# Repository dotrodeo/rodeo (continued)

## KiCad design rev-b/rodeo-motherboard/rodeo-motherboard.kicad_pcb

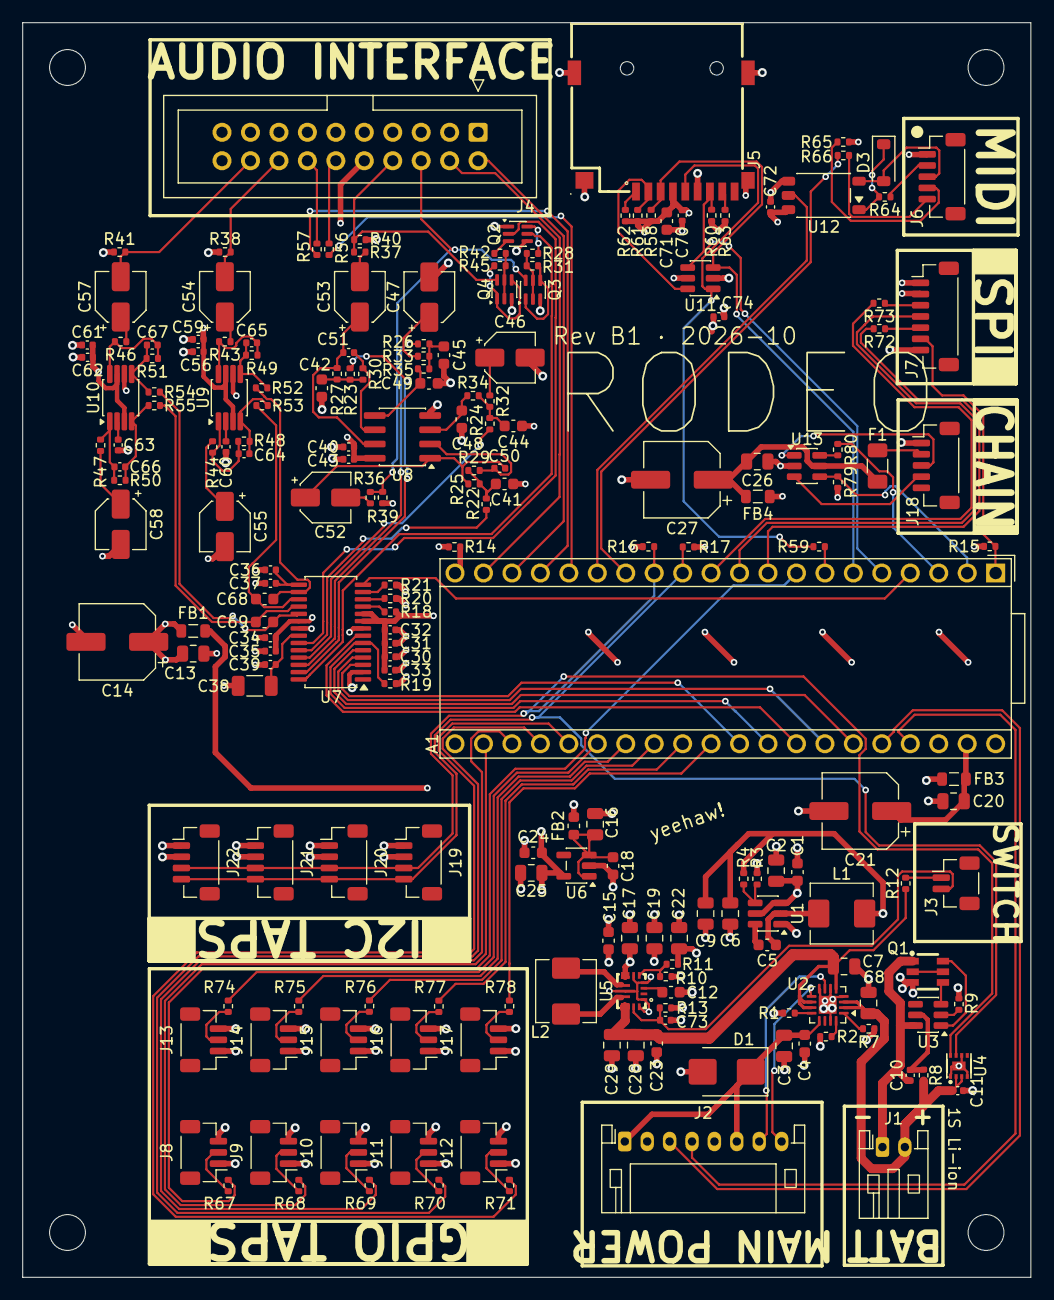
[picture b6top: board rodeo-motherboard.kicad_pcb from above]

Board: 4 copper layers, 90.0 x 112.0 mm, 205 parts (0 on the bottom side), 147 nets.

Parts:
A1: Electrosmith_Daisy_Seed_Rev4; Electrosmith_Daisy_Seed
C1, C5: 0.1u; C_0603_1608Metric
C2, C3, C13, C16, C20, C25, C26, C28, C29: 10u; C_0805_2012Metric
C4, C18, C24: 1u; C_0603_1608Metric
C6, C9, C17, C19, C22: 22u; C_0805_2012Metric
C7, C8: 4.7u; C_0805_2012Metric
C10, C30, C32, C34, C37, C39, C43, C59, C60, C62, C63, C70, C72, C74: 0.1u; C_0402_1005Metric
C11, C31, C33, C35, C36, C40, C56, C61: 1u; C_0402_1005Metric
C12: 100n; C_0603_1608Metric
C14, C21, C27: 100u; CP_Elec_6.3x5.4
C15, C23, C71: 10u; C_0603_1608Metric
C38: 47u; C_1206_3216Metric
C41, C42: 2.2n; C_0603_1608Metric
C44, C45: 6.8n; C_0603_1608Metric
C46, C47, C52, C53: 22u; CP_Elec_4x5.4
C48, C49: 1.5n; C_0603_1608Metric
C50, C51: 470p; C_0402_1005Metric
C54, C55, C57, C58: 10u; CP_Elec_4x5.4
C64, C65, C66, C67: 150p; C_0402_1005Metric
C68, C69: 2.7n; C_0603_1608Metric
C73: 10n; C_0402_1005Metric
D1: SMBJ5.0A; D_SMB
D3: 1N4148W; D_SOD-123
F1: nSMD075; Fuse_1206_3216Metric
FB1, FB3, FB4: BLM21PG221SN1D; L_0805_2012Metric
FB2: BLM18KG601SN1D; L_0603_1608Metric
H1, H2, H3, H4: MountingHole; MountingHole_3.2mm_M3
J1: Conn_01x02; JST_PH_S2B-PH-K_1x02_P2.00mm_Horizontal
J2: Conn_01x08; JST_PH_S8B-PH-K_1x08_P2.00mm_Horizontal
J3: Conn_01x02; JST_SH_BM02B-SRSS-TB_1x02-1MP_P1.00mm_Vertical
J4: Conn_02x10_Odd_Even; IDC-Header_2x10_P2.54mm_Vertical
J5: TF PUSH; TF-SMD_TF-PUSH
J6, J18: Conn_01x05; JST_SH_BM05B-SRSS-TB_1x05-1MP_P1.00mm_Vertical
J7: Conn_01x07; JST_SH_BM07B-SRSS-TB_1x07-1MP_P1.00mm_Vertical
J8, J9, J10, J11, J12, J13, J14, J15, J16, J17: Conn_01x03; JST_SH_BM03B-SRSS-TB_1x03-1MP_P1.00mm_Vertical
J19, J20, J21, J22: Conn_01x04; JST_SH_BM04B-SRSS-TB_1x04-1MP_P1.00mm_Vertical
L1: 2.2uH; L_Sunlord_MWSA0518S
L2: 1.5uH; L_Sunlord_MWSA0518S
Q1: FS8205A; SOT-23-6_L2.9-W1.6-P0.95-LS2.8-BR
Q2: BSS84DW; SOT-363_SC-70-6
Q3, Q4: 2N7002DW; SOT-363_SC-70-6
R1: 1.18K; R_0402_1005Metric
R2: 1.13K; R_0402_1005Metric
R3, R7, R12, R15, R18, R20, R21, R28, R42, R79: 10K; R_0402_1005Metric
R4: 33K2; R_0402_1005Metric
R8, R56, R57, R65, R66: 100R; R_0402_1005Metric
R9, R67, R68, R69, R70, R71, R74, R75, R76, R77, R78: 1K; R_0402_1005Metric
R10: 19K1; R_0402_1005Metric
R11: 100K; R_0402_1005Metric
R13, R31, R38, R41, R45: 1M; R_0402_1005Metric
R14: 0R; R_0402_1005Metric
R16, R17: 2K2; R_0402_1005Metric
R19, R39, R40, R58, R60, R61, R62, R63: 47K; R_0402_1005Metric
R22, R23: 4K42; R_0402_1005Metric
R24, R26: 1K33; R_0402_1005Metric
R25, R27: 4K99; R_0402_1005Metric
R29, R30: 2K32; R_0402_1005Metric
R32, R33: 1K5; R_0402_1005Metric
R34, R35: 715R; R_0402_1005Metric
R36, R37: 560R; R_0402_1005Metric
R43, R44, R46, R47: 7K5; R_0402_1005Metric
R48, R49, R50, R51: 10K5; R_0402_1005Metric
R52, R53, R54, R55: 91R; R_0402_1005Metric
R59: 22R; R_0402_1005Metric
R64: 220R; R_0402_1005Metric
R72, R73, R80: 33R; R_0402_1005Metric
U1: TPS563208; TSOT-23-6
U2: BQ24073RGT; VQFN-16-1EP_3x3mm_P0.5mm_EP1.6x1.6mm
U3: DW01A; SOT-23-6
U4: MAX17048G+T10; TDFN-8_L2.0-W2.0-P0.50-BL-EP1.2
U5: TPS63070RNMR; VQFN-15_L3.0-W2.5-P0.50-BL
U6: TPS7A2033PDBVR; SOT-23-5
U7: CS4272; TSSOP-28_4.4x9.7mm_P0.65mm
U8: OPA2376xxD; SOIC-8_3.9x4.9mm_P1.27mm
U9, U10: THS4521IDGK; VSSOP-8_3x3mm_P0.65mm
U11: SRV05-4; SOT-23-6
U12: TLP2361; SO-5-6_4.55x3.7mm_P1.27mm
U13: USBLC6-2SC6; SOT-23-6

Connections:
+3V3_A: C24.2, C25.2, J7.7, J8.3, J9.3, J10.3, J11.3, J12.3, J13.3, J14.3, J15.3, J16.3, J17.3, U6.5 (OUT)
+3V3_D: C6.2, C9.2, C30.2, C31.2, C32.2, C33.2, C70.1, C71.1, C72.2, C74.1, FB4.1, J5.4 (VDD), J7.1, J19.2, J20.2, J21.2, J22.2, L1.2, R4.2, R15.2, R16.1, R17.1, R18.2, R58.1, R60.1, R61.1, R62.1, R63.1, R65.2, R79.2, U7.9 (VD), U7.10 (VL), U11.5 (VP), U12.6 (VDD)
+3V3_SAT: C26.2, C27.1, F1.2, FB4.2, U13.5 (VBUS)
+5V_A: C13.2, C14.1, C34.2, C35.2, C40.2, C43.1, C56.2, C59.1, C61.2, C62.1, FB1.2, J4.10, Q2.1 (S), Q2.4 (S), U7.20 (VA), U8.8 (V+), U9.3 (V_{S+}), U9.7 (~PD), U10.3 (V_{S+}), U10.7 (~PD)
+5V_SYS: C1.1, C2.1, C15.1, C17.1, C19.1, C22.1, FB1.1, FB2.1, FB3.1, R11.2, U1.3 (VIN), U1.5 (EN), U5.7 (Vout)
AUDIO_IN_1: A1.16 (AUDIO_IN_1), R56.1
AUDIO_IN_2: A1.17 (AUDIO_IN_2), R57.1
AUDIO_OUT_1: A1.18 (AUDIO_OUT_1), J4.2
AUDIO_OUT_2: A1.19 (AUDIO_OUT_2), J4.4
BATT_N: C10.1, J1.1, Q1.1 (S1), U3.6 (GND)
BATT_P: C8.1, C11.1, J1.2, R8.1, U2.2 (BAT), U2.3 (BAT), U4.2 (CELL), U4.3 (VDD)
BATT_VCC: C7.1, C23.1, C28.1, C29.1, R12.1, U2.5 (EN2), U2.10 (OUT), U2.11 (OUT), U5.12 (Vin)
CLK: J5.5 (CLK), R59.1, U11.1 (IO1)
CODEC2_AINA_N: C68.2, R52.1, U7.16 (AINA-)
CODEC2_AINA_P: C68.1, R53.1, U7.17 (AINA+)
CODEC2_AINB_N: C69.2, R54.1, U7.19 (AINB-)
CODEC2_AINB_P: C69.1, R55.1, U7.18 (AINB+)
CODEC2_AOUTA_N: R22.1, U7.24 (AOUTA-)
CODEC2_AOUTA_P: R24.1, U7.25 (AOUTA+)
CODEC2_AOUTB_N: R23.1, U7.27 (AOUTB-)
CODEC2_AOUTB_P: R26.1, U7.26 (AOUTB+)
CODEC2_IN_A: C54.2, J4.16, R38.2
CODEC2_IN_B: C57.2, J4.18, R41.2
CODEC2_LRCK: A1.34 (SAI2_FS), U7.4 (LRCK)
CODEC2_MCLK: A1.31 (SAI2_MCLK), U7.3 (MCLK)
CODEC2_MUTE_A: Q2.2 (G), U7.23 (~AMUTEC)
CODEC2_MUTE_B: Q2.5 (G), U7.28 (~BMUTEC)
CODEC2_OUT_A: J4.6, Q3.6 (D), R36.1, R39.1
CODEC2_OUT_B: J4.8, Q4.6 (D), R37.1, R40.1
CODEC2_RST: A1.4 (SD_DATA_1), U7.14 (~RST)
CODEC2_SCLK: A1.35 (SAI2_SCK), U7.5 (SCLK)
CODEC2_SDIN: A1.33 (SAI2_SD_A), U7.7 (SDIN)
CODEC2_SDOUT: A1.32 (SAI2_SD_B), R19.2, U7.6 (SDOUT(M/~S))
CODEC2_VCOM: C36.2, C37.2, U7.15 (VCOM)
CV_DAC1: A1.30 (DAC_OUT1), R78.2
CV_DAC2: A1.29 (DAC_OUT2), R77.2
DAISY_SCL: A1.12 (I2C1_SCL), J19.4, J20.4, J21.4, J22.4, R17.2, U4.7 (SCL)
DAISY_SDA: A1.13 (I2C1_SDA), J19.3, J20.3, J21.3, J22.3, R16.2, U4.8 (SDA)
DAT3: J5.2 (CD/DAT3), R61.2, U11.6 (IO4)
DIG_1: A1.8 (SPI1_CS), R67.2
DIG_2: A1.22 (ADC_0), R68.2
DIG_3: A1.23 (ADC_1), R69.2
DIG_4: A1.24 (ADC_2), R70.2
DIG_5: A1.25 (ADC_3), R71.2
DIG_6: A1.26 (ADC_4), R74.2
DIG_7: A1.27 (ADC_5), R75.2
DIG_8: A1.28 (ADC_6), R76.2
GND: A1.40 (DGND), C1.2, C2.2, C3.2, C4.2, C6.1, C7.2, C8.2, C9.1, C11.2, C12.2, C13.1, C14.2, C15.2, C16.1, C17.2, C18.1, C19.2, C20.1, C21.2, C22.2, C23.2, C24.1, C25.1, C26.1, C27.2, C28.2, C29.2, C30.1, C31.1, C32.1, C33.1, C34.1, C35.1, C36.1, C37.1, C38.2, C39.1, C40.1, C41.2, C42.2, C43.2, C44.1, C45.1, C46.2, C47.2, C48.2, C49.2, C55.2, C56.1, C58.2, C59.2, C60.2, C61.1, C62.2, C63.2, C70.2, C71.2, C72.1, C73.1, C74.2, D1.2 (A), J2.2, J2.5, J4.1, J4.3, J4.5, J4.7, J4.9, J4.11, J4.13, J4.15, J4.17, J4.19, J5.6 (VSS), J5.10, J5.11, J5.12, J5.13, J6.1, J7.2, J8.1, J9.1, J10.1, J11.1, J12.1, J13.1, J14.1, J15.1, J16.1, J17.1, J18.1, J19.1, J20.1, J21.1, J22.1, Q1.3 (S2), Q3.3 (D), Q4.3 (D), R1.1, R2.1, R3.1, R7.2, R9.2, R10.1, R13.2, R14.1, R19.1, R20.2, R21.2, R38.1, R39.2, R40.2, R41.1, U1.1 (GND), U2.4 (~CE), U2.6 (EN1), U2.8 (VSS), U2.15 (TD), U2.17 (VSS), U4.1 (CTG), U4.4 (GND), U4.6 (QSTRT), U4.9 (EP), U5.1 (PS/SYNC), U5.4 (GND), U5.6 (FB2), U5.10 (PGND), U5.15 (Vsel), U6.2 (GND), U7.2 (XTI), U7.8 (DGND), U7.21 (AGND), U8.4 (V-), U9.6 (V_{S-}), U10.6 (V_{S-}), U11.2 (VN), U12.4 (GND), U13.2 (GND)
GNDA: A1.20 (AGND), R14.2
JACK_IN_1: J4.12, R56.2
JACK_IN_2: J4.14, R57.2
MIDI_IN_R: J6.2, R64.1
MIDI_IN_T: D3.2 (A), J6.3, U12.3 (K)
MIDI_OUT_R: J6.4, R65.1
MIDI_OUT_T: J6.5, R66.1
MIDI_RX: A1.15 (USART1_RX), U12.5 (VO)
MIDI_TX: A1.14 (USART1_TX), R66.2
unnamed: C41.1, R22.2, R25.1, R29.1
unnamed: C42.1, R23.2, R27.1, R30.1
unnamed: C44.2, R24.2, R32.2, R34.2
unnamed: C45.2, R26.2, R33.2, R35.2
unnamed: C46.1, R32.1
unnamed: C47.1, R33.1
unnamed: C50.1, C52.1, R25.2, U8.1
unnamed: C51.1, C53.1, R27.2, U8.7
unnamed: C52.2, R36.2
unnamed: C53.2, R37.2
unnamed: C54.1, R43.1
unnamed: C55.1, R44.1
unnamed: C57.1, R46.1
unnamed: C58.1, R47.1
unnamed: C64.2, R48.2, R53.2, U9.4
unnamed: C65.1, R49.2, R52.2, U9.5
unnamed: C66.2, R50.2, R55.2, U10.4
unnamed: C67.1, R51.2, R54.2, U10.5
unnamed: D3.1 (K), R64.2, U12.1 (A)
unnamed: J3.1, R12.2
unnamed: C73.2, J3.2, R13.1, U5.14 (EN)
unnamed: J5.8 (DAT1), R63.2
unnamed: J5.1 (DAT2), R62.2
unnamed: J7.3, R73.1
unnamed: J7.5, R72.1
unnamed: J8.2, R67.1
unnamed: J9.2, R68.1
unnamed: J10.2, R69.1
unnamed: J11.2, R70.1
unnamed: J12.2, R71.1
unnamed: J13.2, R74.1
unnamed: J14.2, R75.1
unnamed: J15.2, R76.1
unnamed: J16.2, R77.1
unnamed: J17.2, R78.1
unnamed: F1.1, J18.2
unnamed: J18.3, U13.1 (I/O1)
unnamed: J18.4, U13.3 (I/O2)
unnamed: Q1.2 (D1/D2), Q1.5 (D1/D2)
unnamed: Q1.6 (G1), U3.1 (OD)
unnamed: Q1.4 (G2), U3.3 (OC)
unnamed: Q2.6 (D), R28.2
unnamed: Q2.3 (D), R42.2
unnamed: Q3.2 (G), Q3.5 (G), R28.1, R31.1
unnamed: Q3.1 (S), Q3.4 (S), R31.2
unnamed: Q4.2 (G), Q4.5 (G), R42.1, R45.1
unnamed: Q4.1 (S), Q4.4 (S), R45.2
unnamed: R80.1, U13.6 (I/O1)
unnamed: C5.2, L1.1, U1.2 (SW)
unnamed: C5.1, U1.6 (VBST)
unnamed: R3.2, R4.1, U1.4 (VFB)
unnamed: R1.2, U2.12 (ILIM)
unnamed: R2.2, U2.16 (ISET)
unnamed: R7.1, U2.1 (TS)
unnamed: R9.1, U3.2 (CS)
unnamed: C10.2, R8.2, U3.5 (VCC)
unnamed: R10.2, R11.1, U5.5 (FB)
unnamed: L2.1, U5.11 (L1)
unnamed: L2.2, U5.9 (L2)
unnamed: C12.1, U5.3 (Vaux)
unnamed: C16.2, C18.2, FB2.2, U6.1 (IN), U6.3 (EN)
unnamed: R21.1, U7.13 (AD0/~CS(I2S/~LJ))
unnamed: C38.1, C39.2, U7.22 (FILT+)
unnamed: R18.1, U7.11 (SCL/CCLK(M0))
unnamed: R20.1, U7.12 (SDA/CDIN(M1))
unnamed: C48.1, R34.1, U8.3 (+)
unnamed: C50.2, R29.2, U8.2 (-)
unnamed: C49.1, R35.1, U8.5 (+)
unnamed: C51.2, R30.2, U8.6 (-)
unnamed: C65.2, R43.2, R49.1, U9.8 (+)
unnamed: C64.1, R44.2, R48.1, U9.1 (-)
unnamed: C60.1, U9.2 (V_{OCM})
unnamed: C67.2, R46.2, R51.1, U10.8 (+)
unnamed: C66.1, R47.2, R50.1, U10.1 (-)
unnamed: C63.1, U10.2 (V_{OCM})
SAT_RX: A1.2 (SD_DATA_3), R79.1, U13.4 (I/O2)
SAT_TX: A1.3 (SD_DATA_2), R80.2
SD_CLK: A1.7 (SD_CLK), R59.2
SD_CMD: A1.6 (SD_CMD), J5.3 (CMD), R58.2, U11.3 (IO2)
SD_D_0: A1.5 (SD_DATA_0), J5.7 (DAT0), R60.2, U11.4 (IO3)
SEED_VIN: A1.39 (VIN), C20.2, C21.1, FB3.2
SPI_EXT_CS: A1.1 (USB_ID), J7.6, R15.1
SPI_MISO: A1.10 (SPI1_POCI), J7.4
SPI_MOSI: A1.11 (SPI1_PICO), R73.2
SPI_SCK: A1.9 (SPI1_SCK), R72.2
USB_OTG_HS_N: A1.36 (USB_D_-), J2.3
USB_OTG_HS_P: A1.37 (USB_D_+), J2.4
VIN: C3.1, C4.1, D1.1 (K), J2.1, J2.6, U2.13 (IN)
~CHG: J2.8, U2.9 (~CHG)
~PGOOD: J2.7, U2.7 (~PGOOD)

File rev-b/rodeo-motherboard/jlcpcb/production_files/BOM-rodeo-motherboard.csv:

Comment,Designator,Footprint,LCSC,Quantity
0.1u,"C1,C5",C_0603_1608Metric,C14663,2
10u,"C2,C3,C13,C16,C20,C25,C26,C28,C29",C_0805_2012Metric,C15850,9
1u,"C4,C18,C24",C_0603_1608Metric,C15849,3
22u,"C6,C9,C17,C19,C22",C_0805_2012Metric,C45783,5
4.7u,"C7,C8",C_0805_2012Metric,C1779,2
0.1u,"C10,C30,C32,C34,C37,C39,C43,C59,C60,C62,C63,C70,C72,C74",C_0402_1005Metric,C1525,14
1u,"C11,C31,C33,C35,C36,C40,C56,C61",C_0402_1005Metric,C52923,8
100n,C12,C_0603_1608Metric,C14663,1
100u,"C14,C21,C27",CP_Elec_6.3x5.4,C2887276,3
10u,"C15,C23,C71",C_0603_1608Metric,C96446,3
47u,C38,C_1206_3216Metric,C96123,1
2.2n,"C41,C42",C_0603_1608Metric,C296055,2
6.8n,"C44,C45",C_0603_1608Metric,C513559,2
22u,"C46,C47,C52,C53",CP_Elec_4x5.4,C72502,4
1.5n,"C48,C49",C_0603_1608Metric,C107039,2
470p,"C50,C51",C_0402_1005Metric,C106259,2
10u,"C54,C55,C57,C58",CP_Elec_4x5.4,C72484,4
150p,"C64,C65,C66,C67",C_0402_1005Metric,C541469,4
2.7n,"C68,C69",C_0603_1608Metric,C388043,2
10n,C73,C_0402_1005Metric,C15195,1
SMBJ5.0A,D1,D_SMB,C113974,1
1N4148W,D3,D_SOD-123,C81598,1
nSMD075,F1,Fuse_1206_3216Metric,C70078,1
BLM21PG221SN1D,"FB1,FB3,FB4",L_0805_2012Metric,C85840,3
BLM18KG601SN1D,FB2,L_0603_1608Metric,C85833,1
Conn_01x02,J1,JST_PH_S2B-PH-K_1x02_P2.00mm_Horizontal,C173752,1
Conn_01x08,J2,JST_PH_S8B-PH-K_1x08_P2.00mm_Horizontal,C157915,1
Conn_01x02,J3,JST_SH_BM02B-SRSS-TB_1x02-1MP_P1.00mm_Vertical,C160388,1
Conn_02x10_Odd_Even,J4,IDC-Header_2x10_P2.54mm_Vertical,C2977593,1
TF PUSH,J5,TF-SMD_TF-PUSH,C393941,1
Conn_01x05,"J6,J18",JST_SH_BM05B-SRSS-TB_1x05-1MP_P1.00mm_Vertical,C160391,2
Conn_01x07,J7,JST_SH_BM07B-SRSS-TB_1x07-1MP_P1.00mm_Vertical,C160393,1
Conn_01x03,"J8,J9,J10,J11,J12,J13,J14,J15,J16,J17",JST_SH_BM03B-SRSS-TB_1x03-1MP_P1.00mm_Vertical,C160389,10
Conn_01x04,"J19,J20,J21,J22",JST_SH_BM04B-SRSS-TB_1x04-1MP_P1.00mm_Vertical,C160390,4
2.2uH,L1,L_Sunlord_MWSA0518S,C408345,1
1.5uH,L2,L_Sunlord_MWSA0518S,C408344,1
FS8205A,Q1,SOT-23-6_L2.9-W1.6-P0.95-LS2.8-BR,C2830320,1
BSS84DW,Q2,SOT-363_SC-70-6,C161617,1
2N7002DW,"Q3,Q4",SOT-363_SC-70-6,C83571,2
1.18K,R1,R_0402_1005Metric,C270651,1
1.13K,R2,R_0402_1005Metric,C67014,1
10K,"R3,R7,R12,R15,R18,R20,R21,R28,R42,R79",R_0402_1005Metric,C25744,10
33K2,R4,R_0402_1005Metric,C122548,1
100R,"R8,R56,R57,R65,R66",R_0402_1005Metric,C25076,5
1K,"R9,R67,R68,R69,R70,R71,R74,R75,R76,R77,R78",R_0402_1005Metric,C11702,11
19K1,R10,R_0402_1005Metric,C52036,1
100K,R11,R_0402_1005Metric,C25741,1
1M,"R13,R31,R38,R41,R45",R_0402_1005Metric,C26083,5
0R,R14,R_0402_1005Metric,C17168,1
2K2,"R16,R17",R_0402_1005Metric,C25879,2
47K,"R19,R39,R40,R58,R60,R61,R62,R63",R_0402_1005Metric,C25792,8
4K42,"R22,R23",R_0402_1005Metric,C52269,2
1K33,"R24,R26",R_0402_1005Metric,C423242,2
4K99,"R25,R27",R_0402_1005Metric,C25903,2
2K32,"R29,R30",R_0402_1005Metric,C82297,2
1K5,"R32,R33",R_0402_1005Metric,C25867,2
715R,"R34,R35",R_0402_1005Metric,C113474,2
560R,"R36,R37",R_0402_1005Metric,C25126,2
7K5,"R43,R44,R46,R47",R_0402_1005Metric,C25918,4
10K5,"R48,R49,R50,R51",R_0402_1005Metric,C25850,4
91R,"R52,R53,R54,R55",R_0402_1005Metric,C270574,4
22R,R59,R_0402_1005Metric,C25092,1
220R,R64,R_0402_1005Metric,C25091,1
33R,"R72,R73,R80",R_0402_1005Metric,C25105,3
TPS563208,U1,TSOT-23-6,C468250,1
BQ24073RGT,U2,VQFN-16-1EP_3x3mm_P0.5mm_EP1.6x1.6mm,C15220,1
DW01A,U3,SOT-23-6,C351410,1
MAX17048G+T10,U4,TDFN-8_L2.0-W2.0-P0.50-BL-EP1.2,C2682616,1
TPS63070RNMR,U5,VQFN-15_L3.0-W2.5-P0.50-BL,C109322,1
TPS7A2033PDBVR,U6,SOT-23-5,C2862740,1
CS4272,U7,TSSOP-28_4.4x9.7mm_P0.65mm,C2151111,1
OPA2376xxD,U8,SOIC-8_3.9x4.9mm_P1.27mm,C46316,1
THS4521IDGK,"U9,U10",VSSOP-8_3x3mm_P0.65mm,C170157,2
SRV05-4,U11,SOT-23-6,C13612,1
TLP2361,U12,SO-5-6_4.55x3.7mm_P1.27mm,C107626,1
USBLC6-2SC6,U13,SOT-23-6,C7519,1

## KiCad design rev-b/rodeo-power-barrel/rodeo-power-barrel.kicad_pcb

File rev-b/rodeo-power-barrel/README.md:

# Rodeo power board: USB-C + barrel jack

Everything the [USB-C board](../rodeo-power-usbc/README.md) does, plus a barrel
jack for a 9–12 V adapter and a separate 5 V output for LED strips. When the
adapter is plugged in it powers the motherboard; USB stays connected for data
and takes over if the adapter is removed. The contract it meets is in
[`rev-b.md`, "Power"](../rodeo-motherboard/docs/rev-b.md#power).

Designed 2026-10-12. Mounting as the USB-C board: jacks and LEDs on the I/O edge, the board on
the [rear rail](../mounting/README.md) on M3 × 8 mm standoffs.

```
Barrel 7–20 V ─ Q1 reverse-polarity P-FET ─ VBARREL ─┬─ U3 TPS54308 ─ +5V_BRL ─┐
               (TVS D5, bulk C2)                    │                        ├─ U4 TPS2121 ─ VIN ─ J2 (motherboard)
USB-C VBUS ─────────────────────────────────────────┼────────────────────────┘   barrel first
                                                    └─ U2 TPS54302 ─ +5V_AUX ─ F1 3 A PTC ─ J4 (LED strips)
```

## Adapter

5.5 × 2.1 mm plug, **centre positive**, 7–20 V (9 V or 12 V adapters). Full load
is the motherboard (≤1.5 A at 5 V) plus the aux output (≤3 A at 5 V), about
25 W in: **12 V ≥ 2.5 A or 9 V ≥ 3 A**. Smaller adapters work if the aux output
is lightly loaded.

## Connections

Reference designators below are the schematic's (drawn 2026-10-13).

**USB-C section:** identical to the USB-C board (J1, R1/R2 5.1 kΩ CC pull-downs,
U1 USBLC6 flow-through on D+/D−, D3 SMF5.0A and C1 4.7 µF on `VBUS`), except that
`VBUS` goes to the mux (U4 IN2) instead of straight to J2.

**J3, barrel jack: CUI PJ-102AH (C3096093), 5 A, 2.0 mm pin.** Symbol
`Connector:Barrel_Jack_Switch`, footprint
`Connector_BarrelJack:BarrelJack_CUI_PJ-102AH_Horizontal`.

| J3 pin | Net |
|---|---|
| 1 (centre pin) | `BARREL_IN` |
| 2 (sleeve) | `GND` |
| 3 (switch) | no connect: it opens when a plug is inserted, so it must not carry GND |

**Reverse-polarity protection and input filtering.** Only Q1's drain is on the
jack side; everything else is on `VBARREL`, after Q1.

| Part | Connection |
|---|---|
| Q1 AO4407A P-FET, 30 V 12 A (C2841482), symbol `rodeo_power:AO4407A`, SOIC-8 | drain (5–8) `BARREL_IN`; source (1–3) `VBARREL`; gate (4) → R5 100 kΩ to `GND` |
| D4 BZT52C12 12 V Zener (C173429), SOD-123 | cathode `VBARREL`, anode Q1 gate: holds V_GS within −12 V |
| D5 SMBJ20A TVS (C364296), SMB | cathode `VBARREL`, anode `GND` (after Q1, so a reversed adapter can't drive it) |
| C2 47 µF 35 V electrolytic (C72522), 6.3 × 5.4 | `VBARREL` (+) to `GND`: bulk, damps the adapter cable |

With the adapter the right way round, Q1's body diode conducts first, then its
gate is pulled 9–12 V below its source and it turns fully on (≈14 mΩ). Reversed,
the body diode blocks and the gate sits at the source, so Q1 stays off. The
Zener must sit between gate and **source**: tied to the drain it would conduct
with a reversed adapter and turn Q1 on.

**U3, motherboard 5 V: TPS54308 (C168839), 3 A, fixed 350 kHz.** Symbol
`Regulator_Switching:TPS54302` (same pinout; Value TPS54308).

| U3 pin | Connection |
|---|---|
| 3 VIN | `VBARREL`, with 2 × 10 µF 50 V 1206 (C513774) + 0.1 µF 50 V 0603 (C14663) to `GND` at the pin |
| 1 GND | `GND` |
| 5 EN | no connect (internal pull-up enables it) |
| 6 BOOT | C4 0.1 µF 50 V (C14663) to SW |
| 2 SW | L2 10 µH (Sunlord MWSA0603S-100MT, C132141) → `+5V_BRL` |
| 4 FB | R9 100 kΩ from `+5V_BRL`, R8 13.3 kΩ to `GND`: 0.596 × (1 + 100/13.3) = 5.08 V |
| output | C15, C16 22 µF 25 V 0805 (C45783) on `+5V_BRL` |

**U2, LED aux 5 V: TPS54302 (C311983), 3 A.** Same circuit and values as U3:
boot C3, L1, FB R6 100 kΩ / R7 13.3 kΩ, output C17, C18 on `+5V_AUX`. The
TPS54302 pulse-skips at light load, which is efficient and doesn't matter for
LEDs; the motherboard supply uses the fixed-frequency TPS54308 instead.

The buck input caps C9–C14 (four 10 µF, two 0.1 µF) are all on `VBARREL`: in
layout, put one 0.1 µF and two 10 µF at each buck's VIN/GND, 0.1 µF closest.

| Part | Connection |
|---|---|
| F1 3 A PTC, 6 A trip, 1812 (TLC-MSMD300, C262035) | `+5V_AUX` → `AUX_OUT` |
| J4 JST VH 2-pin vertical, B2P-VH (C160315), 10 A | pin 1 `AUX_OUT`, pin 2 `GND` |

**U4, source mux: TPS2121 (C485916), barrel first.** Symbol
`rodeo_power:TPS2121RUXR`. Same configuration the motherboard used before the
mux moved here.

| U4 pin | Connection |
|---|---|
| 7 IN1 (priority) | `+5V_BRL`, C5 1 µF (C15849) to `GND` |
| 2 IN2 | `VBUS`, C6 1 µF (C15849) to `GND` |
| 6 PR1 | R11 28 kΩ from `+5V_BRL`, R10 15 kΩ to `GND` |
| 3 CP2 | R13 34 kΩ from `VBUS`, R12 15 kΩ to `GND` |
| 1, 8 OUT | `VIN`, C8 10 µF 25 V 0805 (C15850) to `GND` |
| 10 ILM | R14 61.9 kΩ to `GND` (≈2 A limit) |
| 11 SS | C7 0.1 µF (C14663) to `GND` |
| 4 OV2, 5 OV1, 9 ST, 12 GND | `GND` |

The barrel side wins while `+5V_BRL` is above ≈0.88 × the USB voltage, so with
5.08 V against USB's 5 V the adapter always takes the load. The mux also stops
either source back-feeding the other.

**J2, to the motherboard:** as on the USB-C board, but pins 1 and 6 are `VIN`
(the mux output), not `VBUS`. Same orientation too: pin 1 at the right in KiCad.

**LEDs:** as on the USB-C board (D1 green `~PGOOD`, D2 red `~CHG`), but R3/R4
go to `VIN`, so they light from either source.

**Mounting:** the board is 60 × 40 mm, with M3 holes
(`MountingHole:MountingHole_3.2mm_M3`) at (5, 15) and (55, 15) mm from the I/O
edge's left end: rail row 1, 50 mm apart. The barrel jack sits between them, so
row 1 works despite its 14 mm depth. J1 overhangs the I/O edge by 0.35 mm, J3 by
0.50 mm. Check with
`tools/kicad/grid_check.py rodeo-power-barrel.kicad_pcb --rear top`.

**3D models for J3 and J4:** KiCad ships no model for the PJ-102AH or the
B2P-VH, so `lib/rodeo_power.pretty` holds copies of KiCad's footprints with
LCSC's models (C3096093, C160315) attached and aligned to the pins.

## Parts (in addition to the USB-C board's, with J2's pins 1/6 moved to VIN)

| Part | Refs | LCSC |
|---|---|---|
| PJ-102AH barrel jack | J3 | C3096093 |
| AO4407A P-FET | Q1 | C2841482 |
| BZT52C12 | D4 | C173429 |
| SMBJ20A | D5 | C364296 |
| 47 µF 35 V electrolytic 6.3×5.4 | C2 | C72522 |
| TPS54308 | U3 | C168839 |
| TPS54302 | U2 | C311983 |
| MWSA0603S-100MT 10 µH | L1, L2 | C132141 |
| 10 µF 50 V 1206 | C9, C10, C12, C13 | C513774 |
| 0.1 µF 50 V 0603 | C3, C4, C7, C11, C14 | C14663 |
| 22 µF 25 V 0805 | C15–C18 | C45783 |
| 100 kΩ 0402 | R5, R6, R9 | C25741 |
| 13.3 kΩ 0402 | R7, R8 | C274352 |
| TLC-MSMD300 3 A PTC | F1 | C262035 |
| B2P-VH | J4 | C160315 |
| TPS2121 | U4 | C485916 |
| 1 µF 50 V 0603 | C5, C6 | C15849 |
| 10 µF 25 V 0805 | C8 | C15850 |
| 28 kΩ 0402 | R11 | C25772 |
| 15 kΩ 0402 | R10, R12 | C25756 |
| 34 kΩ 0402 | R13 | C48939 |
| 61.9 kΩ 0402 | R14 | C25912 |

## Layout

* J1, J3 and the LEDs on the panel edge; J4 (aux) on an inside edge for the LED
  strip cable.
* Each buck: two 10 µF + one 0.1 µF input caps at VIN/GND, SW node and L short, FB divider close to FB
  and away from SW; plenty of GND vias. Keep the bucks (U2, U3) away from the USB pair.
* `VBARREL`, the buck outputs, `VIN` and `AUX_OUT` are power tracks: 1 mm+ or
  pours. The aux path carries 3 A.

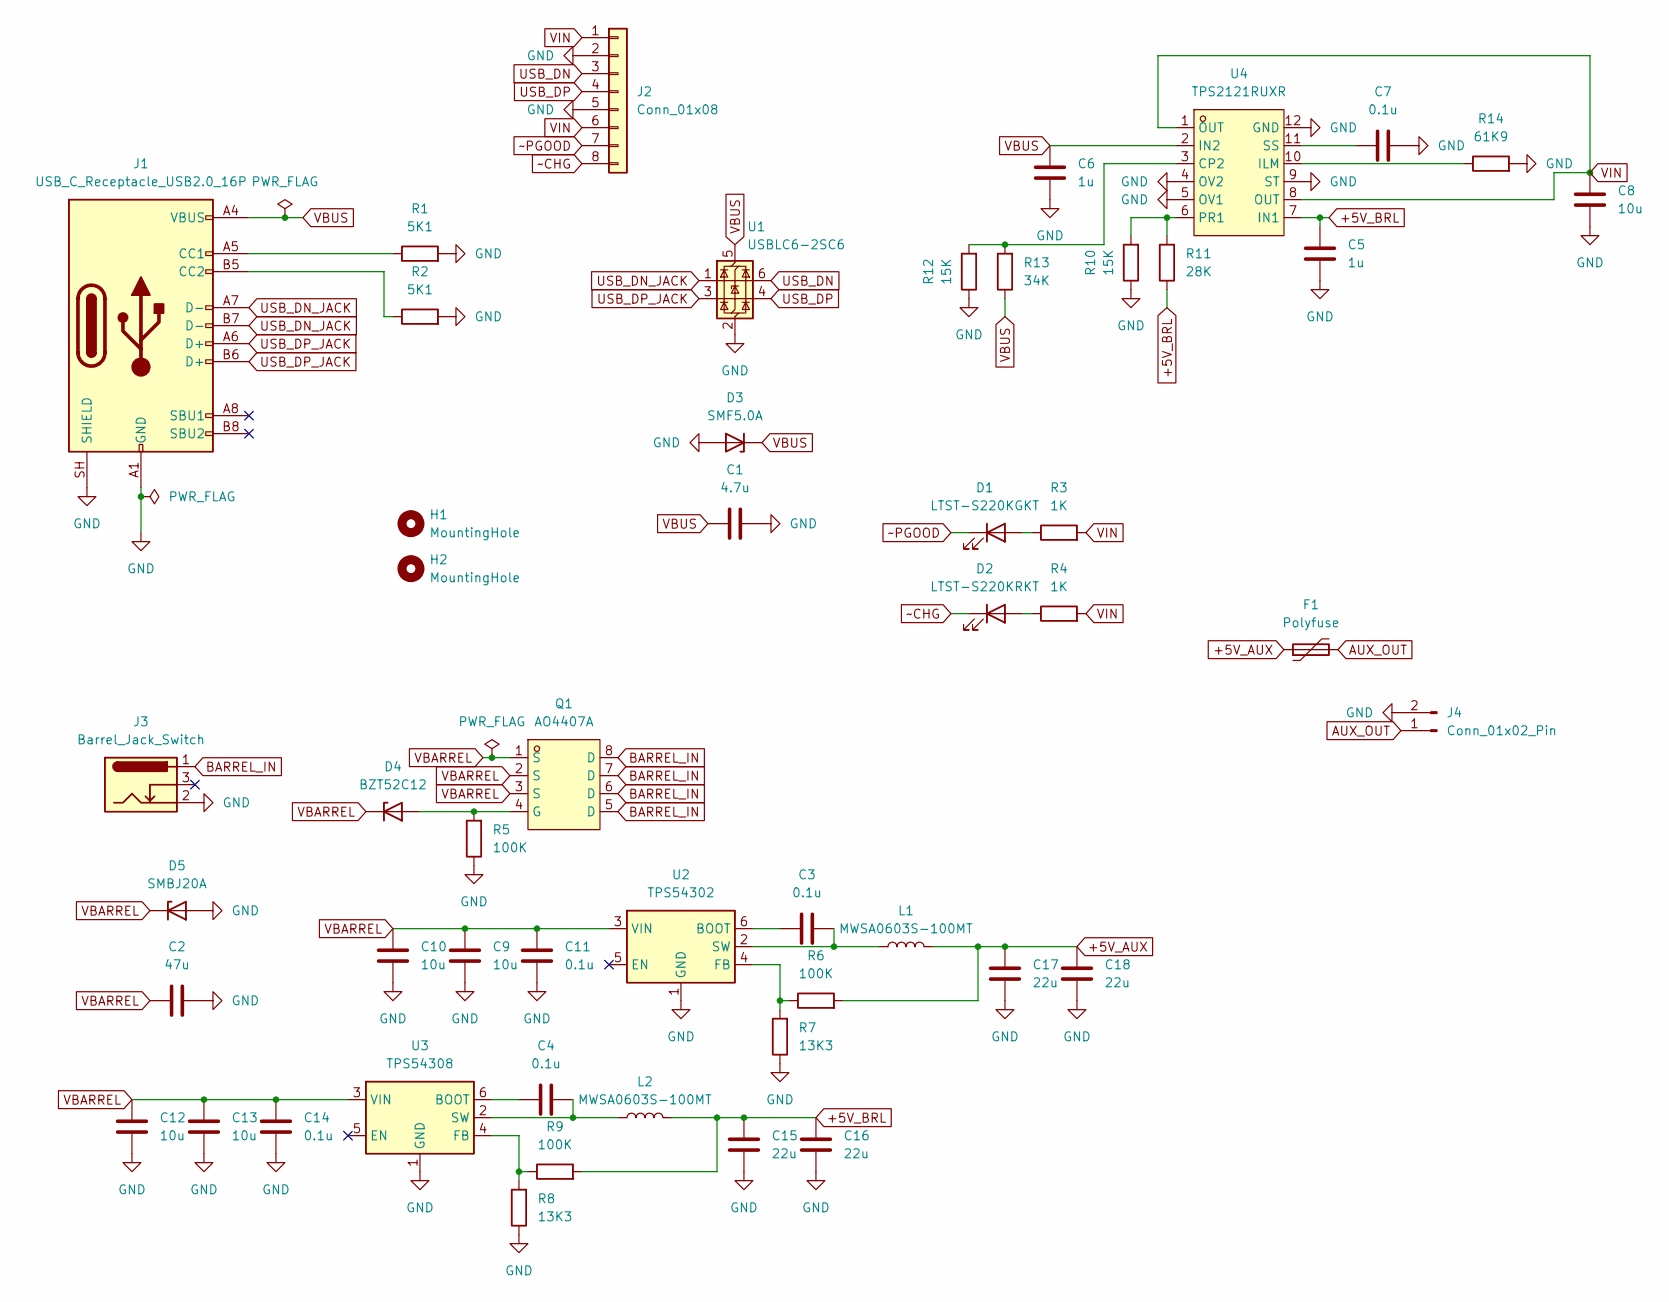
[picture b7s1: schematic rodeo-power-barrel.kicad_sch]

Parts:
C1: 4.7u; C_0603_1608Metric; LCSC Part C69335
C2: 47u; CP_Elec_6.3x5.4; LCSC Part C72522
C3, C4, C7, C11, C14: 0.1u; C_0603_1608Metric; LCSC Part C14663
C5, C6: 1u; C_0603_1608Metric; LCSC Part C15849
C8: 10u; C_0805_2012Metric; LCSC Part C15850
C9, C10, C12, C13: 10u; C_1206_3216Metric; LCSC Part C513774
C15, C16, C17, C18: 22u; C_0805_2012Metric; LCSC Part C45783
D1: LTST-S220KGKT; LED_LiteOn_LTST-S220_SideView; LCSC Part C160469
D2: LTST-S220KRKT; LED_LiteOn_LTST-S220_SideView; LCSC Part C284935
D3: SMF5.0A; D_SOD-123F; LCSC Part C193402
D4: BZT52C12; D_SOD-123; LCSC Part C173429
D5: SMBJ20A; D_SMB; LCSC Part C364296
F1: Polyfuse; Fuse_1812_4532Metric; LCSC Part C262035
H1, H2: MountingHole; MountingHole_3.2mm_M3
J1: USB_C_Receptacle_USB2.0_16P; USB_C_Receptacle_HRO_TYPE-C-31-M-12; LCSC Part C165948
J2: Conn_01x08; JST_PH_B8B-PH-K_1x08_P2.00mm_Vertical; LCSC Part C157974
J3: Barrel_Jack_Switch; BarrelJack_CUI_PJ-102AH_Horizontal; LCSC Part C3096093
J4: Conn_01x02_Pin; JST_VH_B2P-VH_1x02_P3.96mm_Vertical; LCSC Part C160315
L1, L2: MWSA0603S-100MT; L_Sunlord_MWSA0603S; LCSC Part C132141
Q1: AO4407A; SOIC-8_3.9x4.9mm_P1.27mm; MPN AO4407A; LCSC Part C2841482
R1, R2: 5K1; R_0402_1005Metric; LCSC Part C25905
R3, R4: 1K; R_0402_1005Metric; LCSC Part C11702
R5, R6, R9: 100K; R_0402_1005Metric; LCSC Part C25741
R7, R8: 13K3; R_0402_1005Metric; LCSC Part C274352
R10, R12: 15K; R_0402_1005Metric; LCSC Part C25756
R11: 28K; R_0402_1005Metric; LCSC Part C25772
R13: 34K; R_0402_1005Metric; LCSC Part C48939
R14: 61K9; R_0402_1005Metric; LCSC Part C25912
U1: USBLC6-2SC6; SOT-23-6; LCSC Part C7519
U2: TPS54302; TSOT-23-6; LCSC Part C311983
U3: TPS54308; SOT-23-6; LCSC Part C168839
U4: TPS2121RUXR; VQFN-HR-12_L2.5-W2.0-P0.50-BL; MPN TPS2121RUXR; LCSC Part C485916

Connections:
+5V_AUX: C17.2, C18.2, F1.1, L1.2, R6.2
+5V_BRL: C5.2, C15.2, C16.2, L2.2, R9.2, R11.1, U4.7 (IN1)
AUX_OUT: F1.2, J4.1
BARREL_IN: J3.1, Q1.5 (D), Q1.6 (D), Q1.7 (D), Q1.8 (D)
GND: C1.2, C2.2, C5.1, C6.1, C7.1, C8.2, C9.1, C10.1, C11.1, C12.1, C13.1, C14.1, C15.1, C16.1, C17.1, C18.1, D3.2 (A), D5.2 (A), J1.A1 (GND), J1.A12 (GND), J1.B1 (GND), J1.B12 (GND), J1.SH (SHIELD), J2.2, J2.5, J3.2, J4.2, R1.2, R2.2, R5.1, R7.1, R8.1, R10.1, R12.1, R14.2, U1.2 (GND), U2.1 (GND), U3.1 (GND), U4.4 (OV2), U4.5 (OV1), U4.9 (ST), U4.12 (GND)
unnamed: D1.2 (A), R3.1
unnamed: D2.2 (A), R4.1
unnamed: D4.2 (A), Q1.4 (G), R5.2
unnamed: J1.A5 (CC1), R1.1
unnamed: J1.B5 (CC2), R2.1
unnamed: C3.1, U2.6 (BOOT)
unnamed: R6.1, R7.2, U2.4 (FB)
unnamed: C3.2, L1.1, U2.2 (SW)
unnamed: C4.1, U3.6 (BOOT)
unnamed: R8.2, R9.1, U3.4 (FB)
unnamed: C4.2, L2.1, U3.2 (SW)
unnamed: R12.2, R13.2, U4.3 (CP2)
unnamed: R14.1, U4.10 (ILM)
unnamed: R10.2, R11.2, U4.6 (PR1)
unnamed: C7.2, U4.11 (SS)
USB_DN: J2.3, U1.6 (I/O1)
USB_DN_JACK: J1.A7 (D-), J1.B7 (D-), U1.1 (I/O1)
USB_DP: J2.4, U1.4 (I/O2)
USB_DP_JACK: J1.A6 (D+), J1.B6 (D+), U1.3 (I/O2)
VBARREL: C2.1, C9.2, C10.2, C11.2, C12.2, C13.2, C14.2, D4.1 (K), D5.1 (K), Q1.1 (S), Q1.2 (S), Q1.3 (S), U2.3 (VIN), U3.3 (VIN)
VBUS: C1.1, C6.2, D3.1 (K), J1.A4 (VBUS), J1.A9 (VBUS), J1.B4 (VBUS), J1.B9 (VBUS), R13.1, U1.5 (VBUS), U4.2 (IN2)
VIN: C8.1, J2.1, J2.6, R3.2, R4.2, U4.1 (OUT), U4.8 (OUT)
~CHG: D2.1 (K), J2.8
~PGOOD: D1.1 (K), J2.7

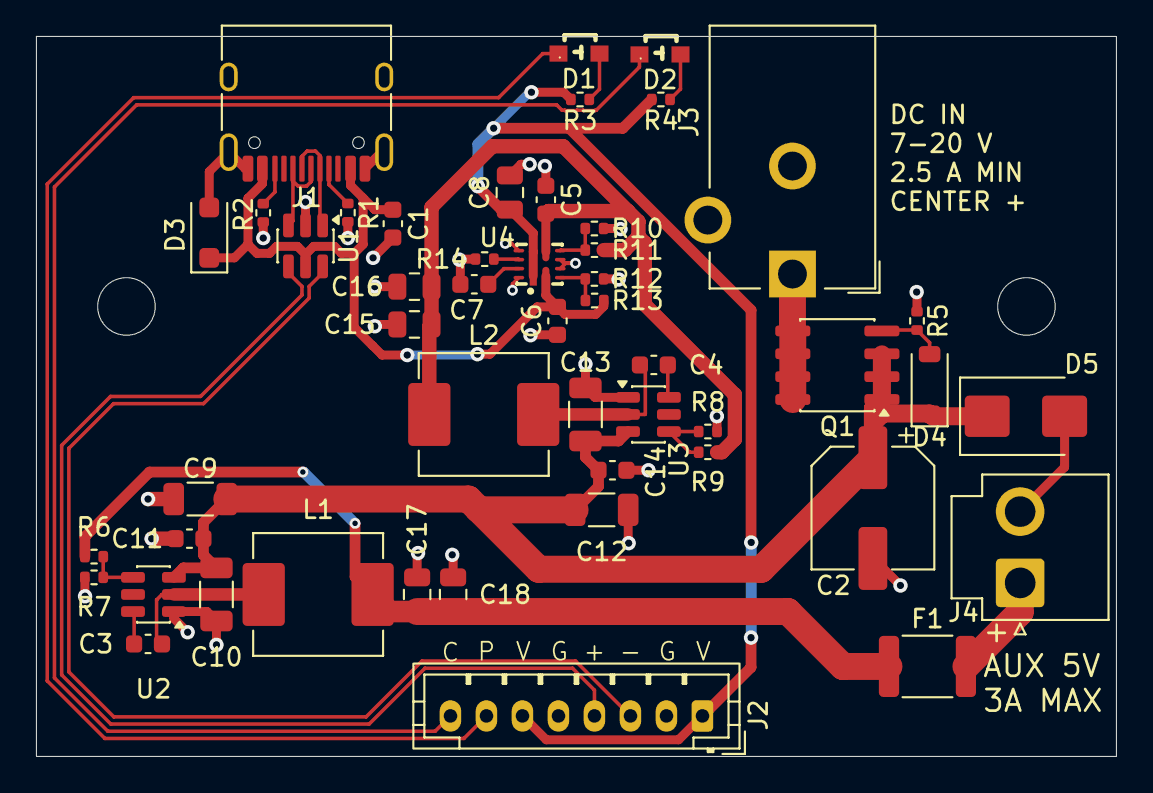
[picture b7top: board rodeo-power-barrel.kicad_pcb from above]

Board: 2 copper layers, 60.0 x 40.0 mm, 51 parts (0 on the bottom side), 29 nets.

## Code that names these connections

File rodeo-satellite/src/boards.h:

#pragma once
//
// What each satellite board wires to which CH32V003F4P6 pin, read from the
// boards' schematics (hardware/rodeo-pot-1, hardware/rodeo-encoder-1,
// hardware/rodeo-pot-bank-4, hardware/rodeo-encoder-bank-4,
// hardware/rodeo-button-bank-4).
// One firmware image serves every board: it reads the ID resistor (kind.h) and
// then uses that kind's map. Pure data, no register access.
//
// Common to every board (contract §1.5):
//   USART1 mapping 0, TX PD5 -> OUT DATA_FWD (33 ohm), RX PD6 <- IN DATA_FWD
//   USART1 mapping 3, TX PC0 -> the DATA_RET tap (33 ohm), RX PC1 (also IN DATA_FWD)
//   SWIO on PD1, the programming pad
//   ID divider read on PD3 (ADC channel 4): R_ID to GND, 10 k on top
//
#include <stdint.h>

#ifdef __cplusplus
extern "C" {
#endif

typedef struct
{
    char    port; // 'A', 'C' or 'D'
    uint8_t pin;
} sat_pin;

#define SAT_NO_PIN ((sat_pin){0, 0})

/** ADC channel for a pin, or -1. CH32V003: A0 PA2, A1 PA1, A2 PC4, A3 PD2,
 *  A4 PD3, A5 PD5, A6 PD6, A7 PD4. */
static inline int8_t sat_adc_channel(sat_pin p)
{
    if(p.port == 'A' && p.pin == 2) return 0;
    if(p.port == 'A' && p.pin == 1) return 1;
    if(p.port == 'C' && p.pin == 4) return 2;
    if(p.port == 'D' && p.pin == 2) return 3;
    if(p.port == 'D' && p.pin == 3) return 4;
    if(p.port == 'D' && p.pin == 5) return 5;
    if(p.port == 'D' && p.pin == 6) return 6;
    if(p.port == 'D' && p.pin == 4) return 7;
    return -1;
}

typedef struct
{
    sat_pin present; // OUT PRESENT: high = nothing downstream, this is the last
    sat_pin led;     // indicator LED, active high
    sat_pin id_feed; // drives the ID divider's 10 k, or port 0 if it's tied to 3V3
    sat_pin pots[4]; // pot wipers, pots 1-4 in slot order; unused ones SAT_NO_PIN
    sat_pin enc_a[4]; // encoders 1-4 in slot order; unused ones SAT_NO_PIN
    sat_pin enc_b[4];
    sat_pin switches; // the push switches' resistor ladder (encoder bank)
    sat_pin buttons[4]; // push switches on their own pins, to GND (button bank)
    sat_pin aux_sense;  // half the aux 5 V, on an ADC pin (button bank)
} sat_board;

/** Kind 1, rodeo-pot-1: the pot bank's map cut to slot 1. One pot on PA2, and
 *  the ID divider fed from PC2 like the bank's. */
#define SAT_BOARD_POT_1                                                        \
    {                                                                          \
        .present = {'C', 3}, .led = {'C', 6}, .id_feed = {'C', 2},             \
        .pots = {{'A', 2}},                                                    \
    }

/** Kind 5, rodeo-pot-bank-4. The ID divider's top is fed from PC2, which the
 *  firmware drives high only while it reads the ID. */
#define SAT_BOARD_POT_BANK_4                                                   \
    {                                                                          \
        .present = {'C', 3}, .led = {'C', 6}, .id_feed = {'C', 2},             \
        .pots = {{'A', 2}, {'D', 2}, {'C', 4}, {'A', 1}},                      \
    }

/** Kind 3, rodeo-encoder-1: the encoder bank's map cut to slot 1. Its push switch
 *  is a one-rung ladder on PD4 (10 k up, 10 k through the switch), and the ID
 *  divider is tied to 3V3 like the bank's. */
#define SAT_BOARD_ENC_1                                                        \
    {                                                                          \
        .present = {'D', 2}, .led = {'D', 0}, .id_feed = {0, 0},               \
        .enc_a = {{'A', 1}}, .enc_b = {{'A', 2}}, .switches = {'D', 4},        \
    }

/** Kind 7, rodeo-button-bank-4. Four switches on their own pins, pulled up
 *  inside the MCU; four WS2812B-2020 LEDs chained from PC6, which only the SPI
 *  driver touches (SPI1's MOSI); AUX_SENSE on PC4. No plain status LED: the RGB
 *  LEDs do IDENTIFY. The ID divider is tied to 3V3. */
#define SAT_BOARD_BUTTON_BANK_4                                                \
    {                                                                          \
        .present = {'C', 3}, .led = {0, 0}, .id_feed = {0, 0},                 \
        .buttons = {{'A', 1}, {'A', 2}, {'D', 4}, {'D', 0}},                   \
        .aux_sense = {'C', 4},                                                 \
    }

/** Kind 6, rodeo-encoder-bank-4. The ID divider's top is tied to 3V3, and PC2
 *  is encoder 2's A line: it must never be driven. The four push switches share
 *  one ADC pin through a resistor ladder (ladder.h). */
#define SAT_BOARD_ENC_BANK_4                                                   \
    {                                                                          \
        .present = {'D', 2}, .led = {'D', 0}, .id_feed = {0, 0},               \
        .enc_a = {{'A', 1}, {'C', 2}, {'C', 4}, {'C', 6}},                     \
        .enc_b = {{'A', 2}, {'C', 3}, {'C', 5}, {'C', 7}},                     \
        .switches = {'D', 4},                                                  \
    }

#ifdef __cplusplus
}
#endif
